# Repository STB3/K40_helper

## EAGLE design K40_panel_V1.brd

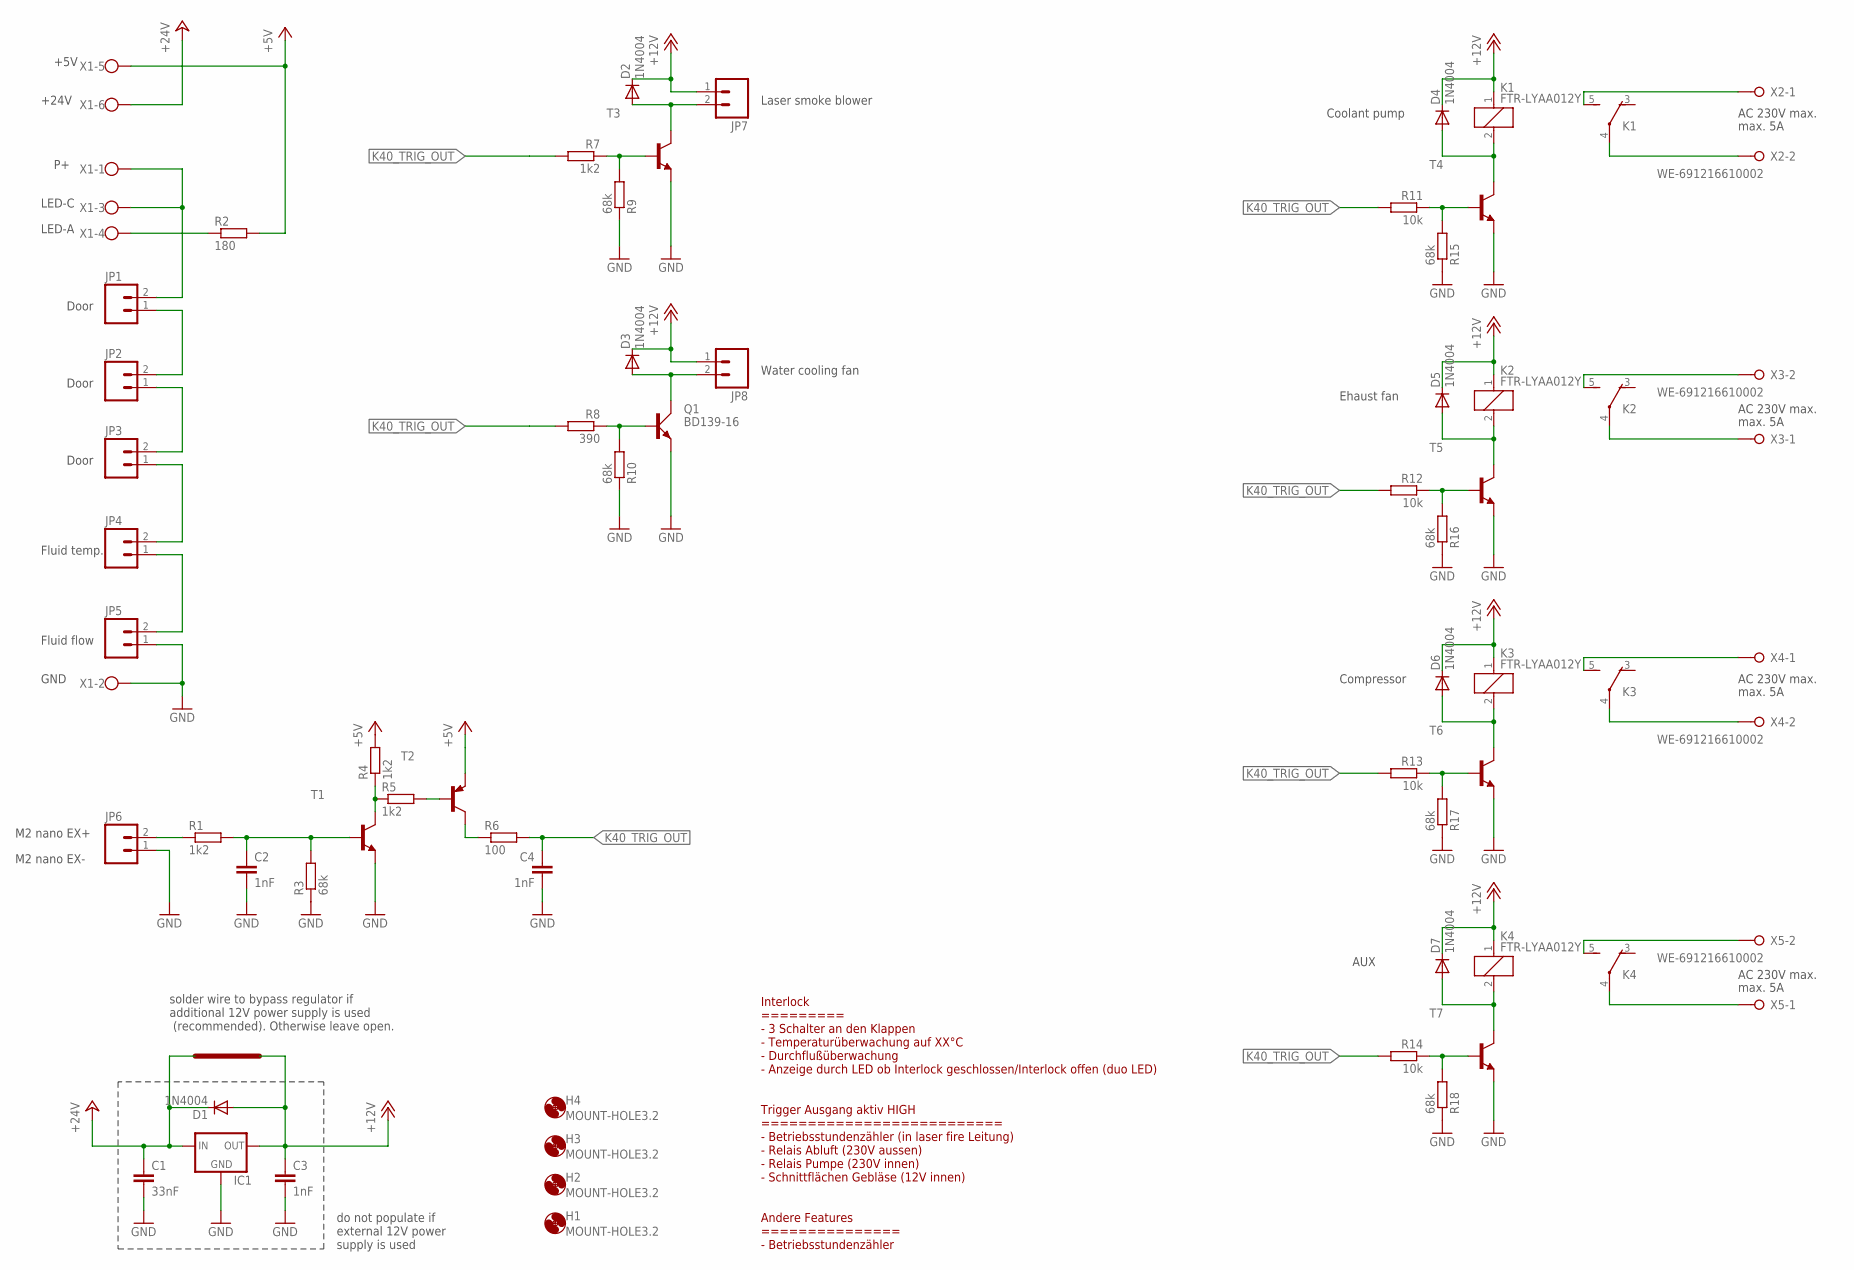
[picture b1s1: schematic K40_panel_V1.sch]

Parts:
C1: 33nF; C050-024X044
C2, C3, C4: 1nF; C050-024X044
D1, D2, D3, D4, D5, D6, D7: 1N4004; DO41-10
H1, H2, H3, H4: MOUNT-HOLE3.2; 3,2
IC1: 78XXS
JP1, JP2, JP3, JP4, JP5, JP6, JP7, JP8: M02POLAR; MOLEX-1X2
K1, K2, K3, K4: FTR-LYAA012Y; FTR-LYC
Q1: BD139-16; TO126AV
R1, R4, R5, R7: 1k2; 0204/7
R2: 180; 0204/7
R3, R9, R10, R15, R16, R17, R18: 68k; 0204/7
R6: 100; 0204/7
R8: 390; 0204/7
R11, R12, R13, R14: 10k; 0204/7
T1, T3, T4, T5, T6, T7: 2N4401-NPN-TO92-EBC; TO92-EBC
T2: 2N4403-PNP-TO92-EBC; TO92-EBC
X1: W237-6
X2, X3, X4, X5: WE-691216610002; W237-2N

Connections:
+5V: R2.2, R4.2, T2.E, X1.5
+12V: C3.1, D1.A, D2.C, D3.C, D4.C, D5.C, D6.C, D7.C, IC1.OUT, JP7.1, JP8.1, K1.1, K2.1, K3.1, K4.1
+24V: C1.1, D1.C, IC1.IN, X1.6
GND: C1.2, C2.2, C3.2, C4.2, IC1.GND, JP5.1, JP6.1, Q1.E, R3.1, R9.1, R10.1, R15.1, R16.1, R17.1, R18.1, T1.E, T3.E, T4.E, T5.E, T6.E, T7.E, X1.2
K40_TRIG_OUT: C4.1, R6.2, R7.2, R8.2, R11.2, R12.2, R13.2, R14.2
unnamed: JP1.2, X1.1, X1.3
unnamed: JP1.1, JP2.2
unnamed: JP2.1, JP3.2
unnamed: JP3.1, JP4.2
unnamed: JP4.1, JP5.2
unnamed: JP6.2, R1.1
unnamed: R2.1, X1.4
unnamed: C2.1, R1.2, R3.2, T1.B
unnamed: R4.1, R5.1, T1.C
unnamed: D2.A, JP7.2, T3.C
unnamed: R7.1, R9.2, T3.B
unnamed: D6.A, K3.2, T6.C
unnamed: R5.2, T2.B
unnamed: R6.1, T2.C
unnamed: R13.1, R17.2, T6.B
unnamed: K1.4, X2.2
unnamed: D7.A, K4.2, T7.C
unnamed: D4.A, K1.2, T4.C
unnamed: D5.A, K2.2, T5.C
unnamed: R14.1, R18.2, T7.B
unnamed: K1.5 (S), X2.1
unnamed: R11.1, R15.2, T4.B
unnamed: K2.5 (S), X3.2
unnamed: K2.4, X3.1
unnamed: R12.1, R16.2, T5.B
unnamed: K3.5 (S), X4.1
unnamed: K3.4, X4.2
unnamed: K4.5 (S), X5.2
unnamed: K4.4, X5.1
unnamed: D3.A, JP8.2, Q1.C
unnamed: Q1.B, R8.1, R10.2

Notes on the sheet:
Interlock ========= - 3 Schalter an den Klappen - Temperaturüberwachung auf XX°C - Durchflußüberwachung - Anzeige durch LED ob Interlock geschlossen/Interlock offen (duo LED) Trigger Ausgang aktiv HIGH ========================== - Betriebsstundenzähler (in laser fire Leitung) - Relais Abluft (230V 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
Door
Fluid temp.
Fluid flow
GND
LED-C
+5V
LED-A
+24V
Laser smoke blower
Coolant pump
Ehaust fan
Compressor
AUX
max. 5A
AC 230V max.
Water cooling fan
solder wire to bypass regulator if additional 12V power supply is used (recommended). Otherwise leave open.
do not populate if external 12V power supply is used
M2 nano EX+
M2 nano EX-

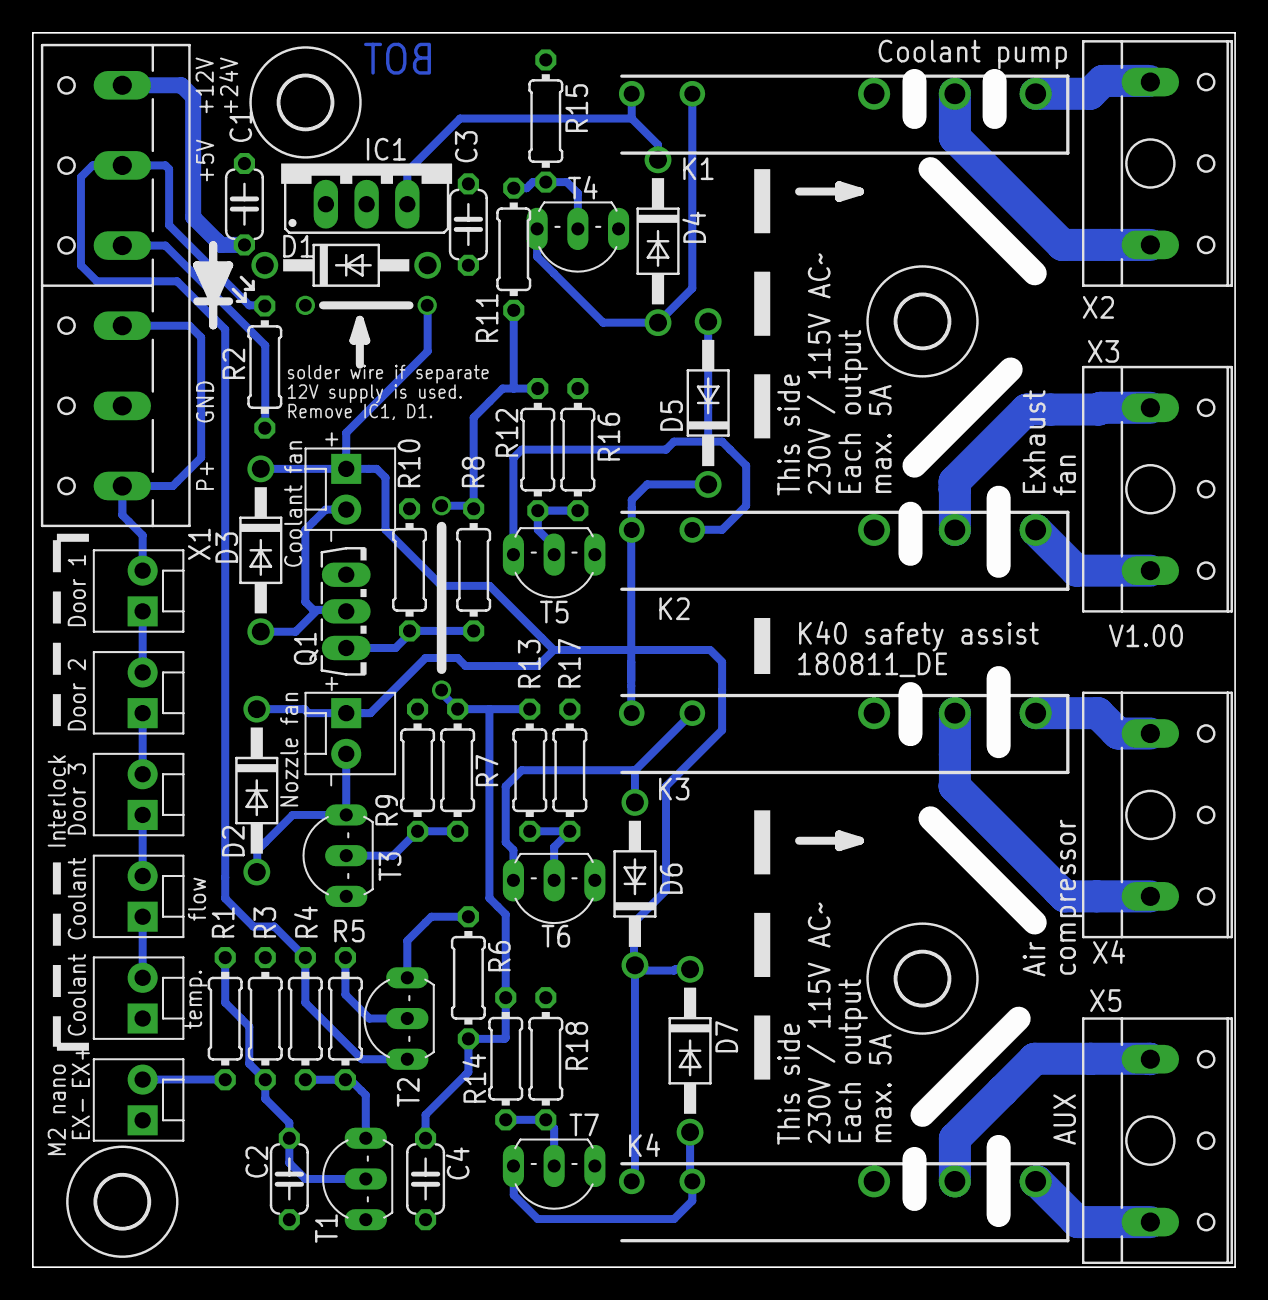
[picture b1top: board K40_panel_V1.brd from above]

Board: 1 copper layer, 73.6 x 75.6 mm, 59 parts (0 on the bottom side), 36 nets.

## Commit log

2018-09-03 Initial version
2018-09-03 Add BOM
